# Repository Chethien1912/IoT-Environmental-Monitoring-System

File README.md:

# IoT Environmental Monitoring System

Hệ thống giám sát môi trường thời gian thực sử dụng ESP32, được thiết kế để đo và theo dõi các thông số nhiệt độ, độ ẩm, khí CO và khí NO2. Dự án kết hợp phần cứng nhúng, giao diện hiển thị tại thiết bị, backend lưu trữ dữ liệu và ứng dụng giám sát từ xa, phù hợp cho các mô hình phòng thí nghiệm, lớp học, nhà xưởng nhỏ hoặc khu vực cần cảnh báo chất lượng không khí cục bộ.

Thiết bị có thể hoạt động độc lập với màn hình cảm ứng tại chỗ, đồng thời đồng bộ dữ liệu lên backend khi có WiFi. Người dùng có thể quan sát thông số đo, thay đổi ngưỡng cảnh báo, chuyển chế độ điều khiển tự động/thủ công và theo dõi trạng thái relay, buzzer thông qua giao diện thiết bị hoặc ứng dụng.

## Hình ảnh dự án

| Mặt trước thiết bị | Góc nhìn tổng thể |
| --- | --- |
|  |  |

| Giao diện chế độ tự động | Giao diện chế độ thủ công |
| --- | --- |
|  |  |

## Chức năng chính

- Đo nhiệt độ và độ ẩm bằng cảm biến SHT31.
- Đo nồng độ khí CO và NO2 qua ngõ ADC của ESP32.
- Hiển thị dữ liệu trực tiếp trên màn hình TFT cảm ứng.
- Quản lý thời gian bằng RTC DS3231 và có thể đồng bộ NTP khi kết nối mạng.
- Điều khiển 3 relay và buzzer theo hai chế độ:
  - `Auto`: tự động bật/tắt relay dựa trên ngưỡng nhiệt độ, độ ẩm, CO và NO2.
  - `Manual`: người dùng bật/tắt relay trực tiếp trên màn hình hoặc từ ứng dụng.
- Cho phép chỉnh ngưỡng cảnh báo ngay trên thiết bị.
- Kết nối WiFi, gửi telemetry lên backend và nhận trạng thái điều khiển từ server.
- Backend hỗ trợ REST API, MQTT, Socket.IO realtime, xác thực JWT và lưu dữ liệu bằng SQLite.
- Ứng dụng Flutter dùng để đăng nhập, xem danh sách thiết bị, theo dõi chỉ số và quản lý điều khiển từ xa.
- Có thiết kế PCB bằng KiCad và mô hình cơ khí bằng SolidWorks/STEP.

## Kiến trúc hệ thống

```text
ESP32 + cảm biến + relay + buzzer + TFT
        |
        | HTTP / WiFi
        v
Backend Fastify + SQLite + MQTT + Socket.IO
        |
        | REST API / realtime
        v
Ứng dụng Flutter giám sát và điều khiển
```

Firmware ESP32 được tổ chức theo các module riêng cho cảm biến, WiFi, RTC, relay, giao diện và bộ điều phối chính. `AppController` chạy nhiều task FreeRTOS để tách riêng cập nhật giao diện, đọc cảm biến, điều khiển relay và đồng bộ backend, giúp thiết bị phản hồi ổn định hơn khi vừa hiển thị vừa truyền dữ liệu.

Backend đóng vai trò trung gian lưu dữ liệu thiết bị, quản lý trạng thái điều khiển mong muốn, nhận telemetry từ ESP32 và phát cập nhật realtime cho ứng dụng. Frontend Flutter cung cấp giao diện đăng nhập, danh sách thiết bị, trang chi tiết thiết bị, biểu đồ/chỉ số đo và quản lý người dùng.

## Cấu trúc thư mục

```text
.
├── Code/
│   ├── backend/backend/          # Backend Fastify, SQLite, MQTT, Socket.IO
│   ├── firmware/IoT_ESP32_Local/ # Firmware ESP32 Arduino/C++
│   └── frontend/                 # Ứng dụng Flutter
├── PCB/                          # File thiết kế PCB KiCad, BOM và Gerber
├── Solidwork/                    # Mô hình cơ khí và file STEP
├── images/                       # Hình ảnh thiết bị và giao diện thực tế
├── LICENSE
└── README.md
```

## Công nghệ sử dụng

- Phần cứng: ESP32, SHT31, cảm biến khí CO/NO2, RTC DS3231, TFT cảm ứng, relay, buzzer.
- Firmware: Arduino/C++, FreeRTOS task, HTTPClient, WiFi, giao diện cảm ứng.
- Backend: Node.js, Fastify, SQLite (`better-sqlite3`), JWT, MQTT.js, Socket.IO.
- Frontend: Flutter, Material 3, REST API.
- Thiết kế phần cứng: KiCad, SolidWorks.

## Chạy backend

```bash
cd Code/backend/backend
npm install
npm run seed
npm run dev
```

Backend mặc định chạy tại:

```text
http://localhost:3000
```
Tài khoản mặc định sau khi seed:

```text
Username: admin
Password: Admin@123
```
## Firmware ESP32
Firmware nằm tại:

```text
Code/firmware/IoT_ESP32_Local
```
Mở file `IoT_ESP32_Local.ino` bằng Arduino IDE hoặc môi trường tương thích ESP32, cài các thư viện cần thiết cho màn hình TFT, cảm ứng, WiFi và cảm biến, sau đó nạp chương trình vào ESP32. Khi thiết bị khởi động, hệ thống sẽ đọc cảm biến định kỳ, cập nhật màn hình, xử lý điều khiển relay/buzzer và đồng bộ dữ liệu với backend nếu đã cấu hình WiFi và Backend URL.

## Ứng dụng Flutter
Ứng dụng nằm tại:

```text
Code/frontend
```
Chạy ứng dụng:
```bash
cd Code/frontend
flutter pub get
flutter run
```
Ứng dụng dùng API backend để đăng nhập, lấy danh sách thiết bị, xem dữ liệu realtime và gửi lệnh điều khiển.

## Ghi chú
- Cấu hình backend có thể tham khảo trong `Code/backend/backend/.env.example`.
- File thiết kế PCB, BOM và Gerber nằm trong thư mục `PCB`.
- Mô hình cơ khí của thiết bị nằm trong thư mục `Solidwork`.
- Thiết bị có thể hoạt động cục bộ trên màn hình cảm ứng ngay cả khi chưa kết nối backend, nhưng cần WiFi và Backend URL để đồng bộ dữ liệu từ xa.

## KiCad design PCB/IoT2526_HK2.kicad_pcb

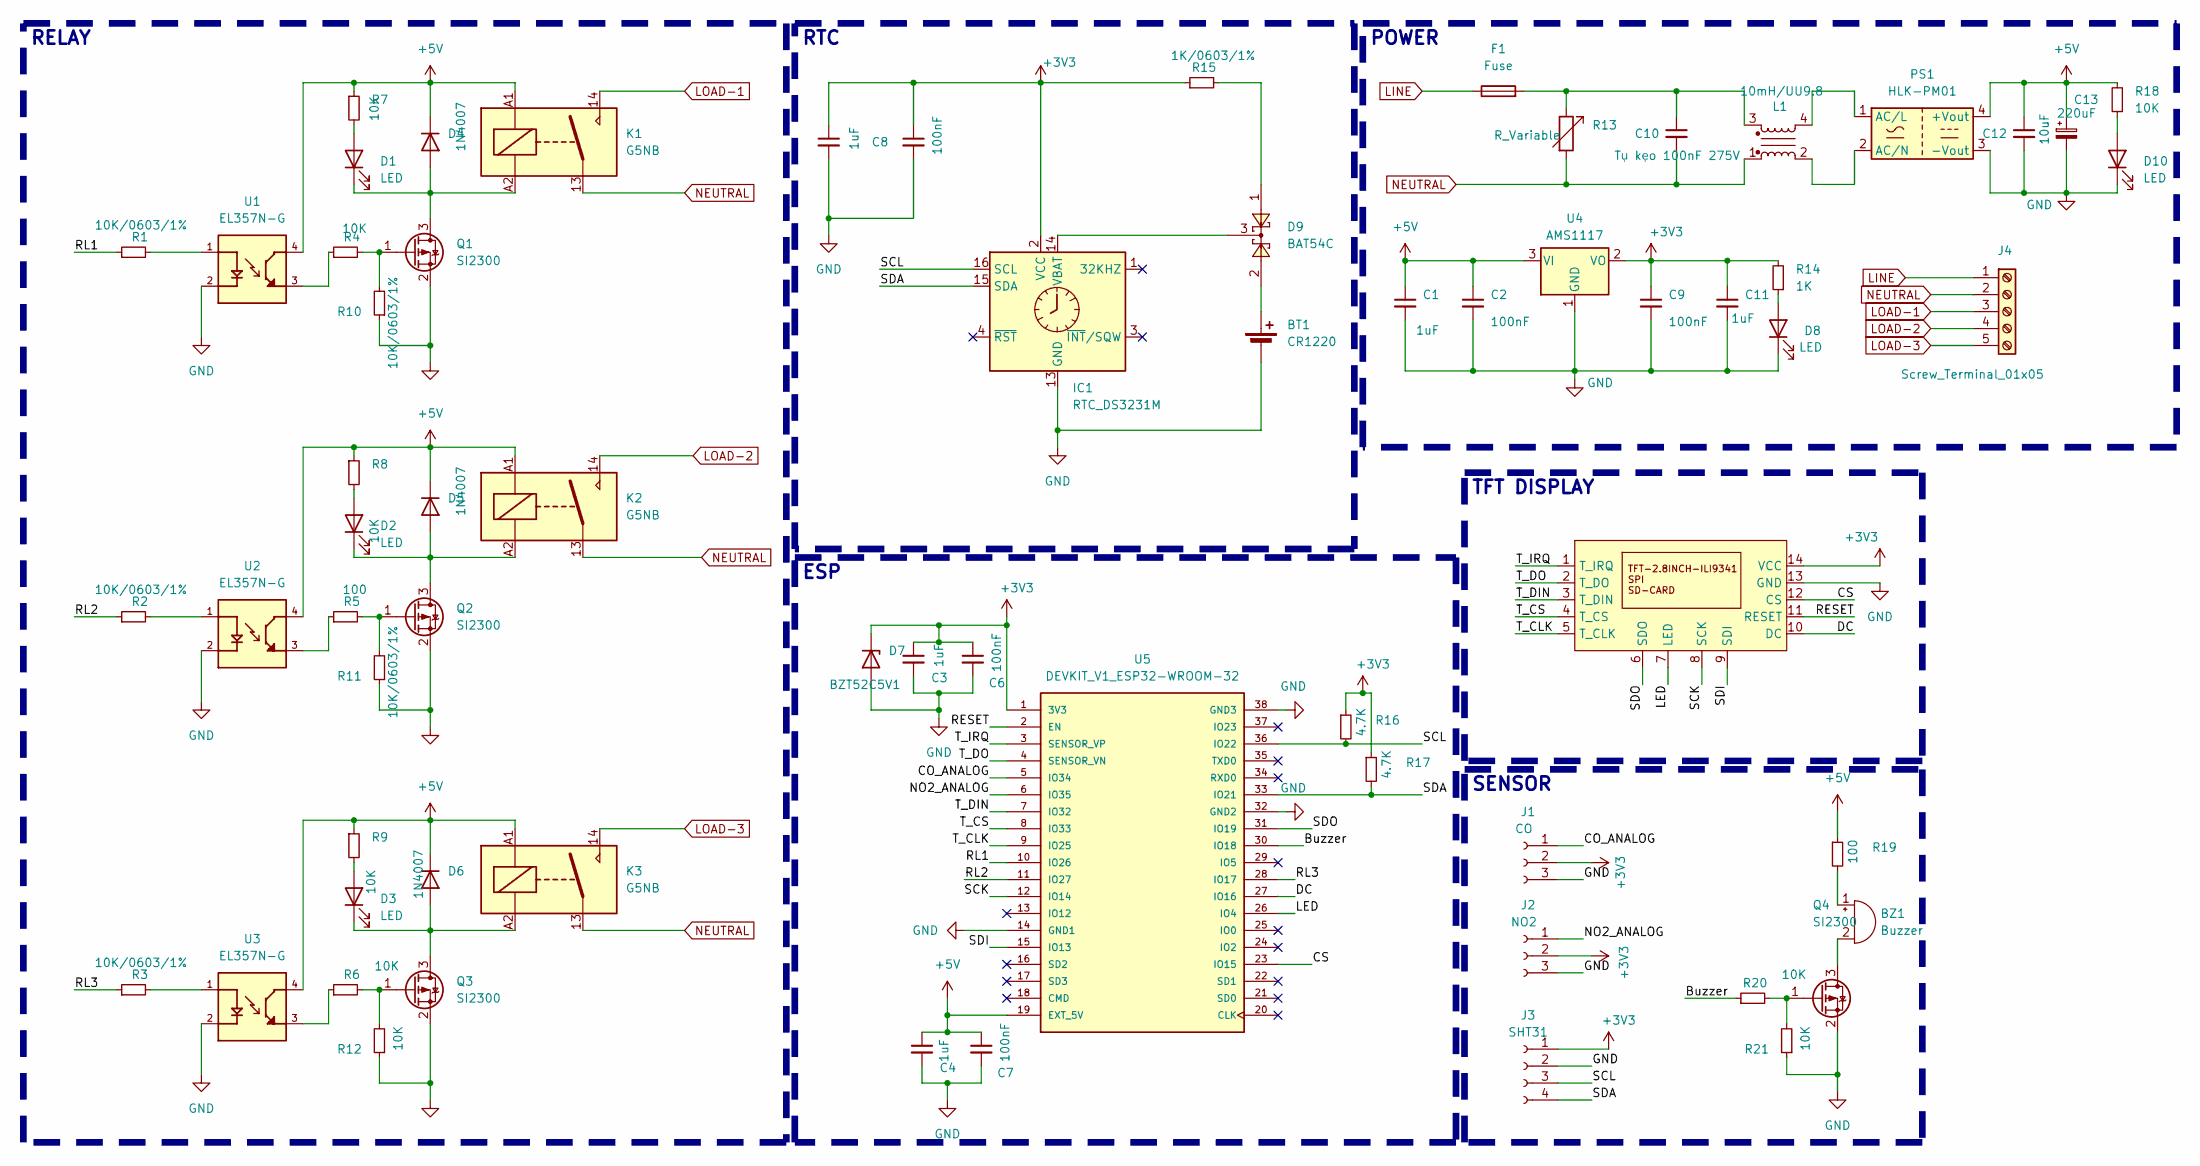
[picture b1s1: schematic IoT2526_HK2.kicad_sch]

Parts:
BT1: CR1220; BatteryHolder-SMD-CR1220
BZ1: Buzzer; Buzzer-THT-12x9.5_RM7.6
C1, C3, C4, C5, C11: 1uF; C_0603
C2, C6, C7, C8, C9: 100nF; C_0603
C10: Tụ kẹo 100nF 275V; C-Polyester-Rect-L16.5mm-W5.0mm-P15.00mm-MKT
C12: 10uF; C_0603
C13: 220uF; CP_Elec_8x10.5
D1, D2, D3, D8, D10: LED; LED_0603_1608Metric
D4, D5, D6: 1N4007; D_SOD-123F
D7: BZT52C5V1; D_SOD-123
D9: BAT54C; SOT23-3
F1: Fuse; Fuse_Bourns_MF-RG300
IC1: RTC_DS3231M; SOIC-16W_7.5x10.3mm_P1.27mm
J1: CO; PinSocket_1x03_P2.54mm_Vertical
J2: NO2; PinSocket_1x03_P2.54mm_Vertical
J3: SHT31; PinSocket_1x04_P2.54mm_Vertical
J4: Screw_Terminal_01x05; HB9500-5P
K1, K2, K3: G5NB; Relay_SPST_Omron_G5NB
L1: 10mH/UU9.8; ACFilterChoke-UU9.8
PS1: HLK-PM01; Converter_ACDC_Hi-Link_HLK-PMxx
Q1, Q2, Q3, Q4: SI2300; SOT-23
R1, R2, R3, R10, R11: 10K/0603/1%; R_0603
R4, R6, R7, R8, R9, R12, R18, R20, R21: 10K; R_0603
R5, R19: 100; R_0603
R13: R_Variable; Varistor-RV-Disc-D12mm-W5.8mm-P7.5mm
R14: 1K; R_0603
R15: 1K/0603/1%; R_0603
R16, R17: 4.7K; R_0603
U1, U2, U3: EL357N-G; OPTO_EL357N-G; PARTREV 6
U4: AMS1117; SOT233
U5: DEVKIT_V1_ESP32-WROOM-32; MODULE_DEVKIT_V1_ESP32-WROOM-32; PARTREV N/A
U6: TFT-ILI9341

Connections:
+3V3: C3.1, C5.1, C6.1, C8.1, C9.1, C11.1, D7.1 (K), IC1.2 (VCC), J1.2, J2.2, J3.1, R14.2, R15.1, R16.1, R17.1, U4.2 (VO), U5.1 (3V3), U6.14 (VCC)
+5V: C1.1, C2.1, C4.1, C7.1, C12.1, C13.1, D4.1 (K), D5.1 (K), D6.1 (K), K1.A1, K2.A1, K3.A1, PS1.4 (+Vout), R7.1, R8.1, R9.1, R18.2, R19.1, U1.4, U2.4, U3.4, U4.3 (VI), U5.19 (EXT_5V)
/Buzzer: R20.1, U5.30 (IO18)
/CO_ANALOG: J1.1, U5.5 (IO34)
/CS: U5.23 (IO15), U6.12 (CS)
/DC: U5.27 (IO16), U6.10 (DC)
/LED: U5.26 (IO4), U6.7 (LED)
/NO2_ANALOG: J2.1, U5.6 (IO35)
/RESET: U5.2 (EN), U6.11 (RESET)
/RL1: R1.1, U5.10 (IO26)
/RL2: R2.1, U5.11 (IO27)
/RL3: R3.1, U5.28 (IO17)
/SCK: U5.12 (IO14), U6.8 (SCK)
/SCL: IC1.16 (SCL), J3.3, R16.2, U5.36 (IO22)
/SDA: IC1.15 (SDA), J3.4, R17.2, U5.33 (IO21)
/SDI: U5.15 (IO13), U6.9 (SDI)
/SDO: U5.31 (IO19), U6.6 (SDO)
/T_CLK: U5.9 (IO25), U6.5 (T_CLK)
/T_CS: U5.8 (IO33), U6.4 (T_CS)
/T_DIN: U5.7 (IO32), U6.3 (T_DIN)
/T_DO: U5.4 (SENSOR_VN), U6.2 (T_DO)
/T_IRQ: U5.3 (SENSOR_VP), U6.1 (T_IRQ)
GND: BT1.2 (-), C1.2, C2.2, C3.2, C4.2, C5.2, C6.2, C7.2, C8.2, C9.2, C11.2, C12.2, C13.2, D7.2 (A), D8.1 (K), D10.1 (K), IC1.5 (GND), IC1.6 (GND), IC1.7 (GND), IC1.8 (GND), IC1.9 (GND), IC1.10 (GND), IC1.11 (GND), IC1.12 (GND), IC1.13 (GND), J1.3, J2.3, J3.2, PS1.3 (-Vout), Q1.2 (S), Q2.2 (S), Q3.2 (S), Q4.2 (S), R10.1, R11.1, R12.1, R21.1, U1.2, U2.2, U3.2, U4.1 (GND), U5.14 (GND1), U5.32 (GND2), U5.38 (GND3), U6.13 (GND)
LINE: F1.1, J4.1
LOAD-1: J4.3, K1.14
LOAD-2: J4.4, K2.14
LOAD-3: J4.5, K3.14
NEUTRAL: C10.2, J4.2, K1.13, K2.13, K3.13, L1.1, R13.2
unnamed: BT1.1 (+), D9.2
unnamed: BZ1.1 (+), R19.2
unnamed: BZ1.2 (-), Q4.3 (D)
unnamed: C10.1, F1.2, L1.3, R13.1
unnamed: D1.2 (A), R7.2
unnamed: D1.1 (K), D4.2 (A), K1.A2, Q1.3 (D)
unnamed: D2.2 (A), R8.2
unnamed: D2.1 (K), D5.2 (A), K2.A2, Q2.3 (D)
unnamed: D3.2 (A), R9.2
unnamed: D3.1 (K), D6.2 (A), K3.A2, Q3.3 (D)
unnamed: D8.2 (A), R14.1
unnamed: D9.1, R15.2
unnamed: D10.2 (A), R18.1
unnamed: D9.3, IC1.14 (VBAT)
unnamed: L1.4, PS1.1 (AC/L)
unnamed: L1.2, PS1.2 (AC/N)
unnamed: Q1.1 (G), R4.2, R10.2
unnamed: Q2.1 (G), R5.2, R11.2
unnamed: Q3.1 (G), R6.2, R12.2
unnamed: Q4.1 (G), R20.2, R21.2
unnamed: R1.2, U1.1
unnamed: R2.2, U2.1
unnamed: R3.2, U3.1
unnamed: R4.1, U1.3
unnamed: R5.1, U2.3
unnamed: R6.1, U3.3

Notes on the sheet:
RELAY
SENSOR
TFT DISPLAY
ESP
RTC
POWER

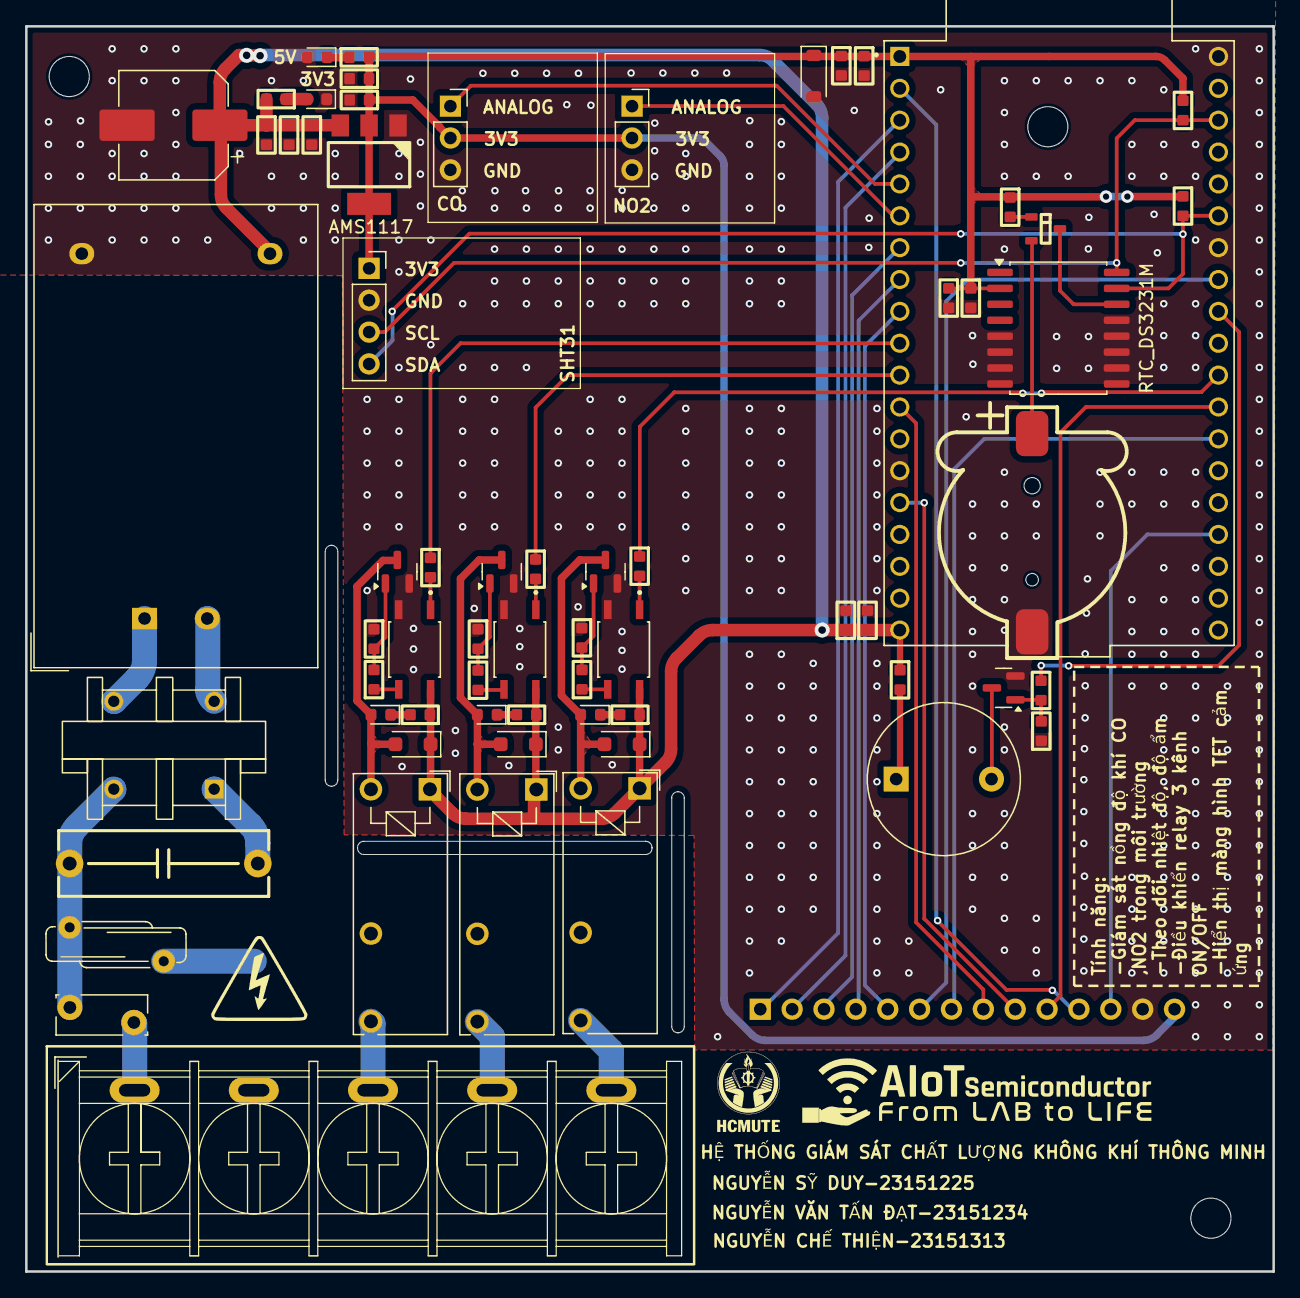
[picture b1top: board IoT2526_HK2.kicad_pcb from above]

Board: 2 copper layers, 99.4 x 99.2 mm, 67 parts (1 on the bottom side), 54 nets.

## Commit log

2026-05-18 Add firmware, PCB, and SolidWorks files
2026-05-18 Reorganize project folders

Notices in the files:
parts and their libraries:
Copyright 2021 Accelerated Designs. All rights reserved.
